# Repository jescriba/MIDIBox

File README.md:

MIDIBox is a basic midi controller with audio playback capabilities implemented for the AVR embedded environment _without_ Arduino libraries. 

Intro blog: https://jescriba.github.io/2019/12/22/midibox.html

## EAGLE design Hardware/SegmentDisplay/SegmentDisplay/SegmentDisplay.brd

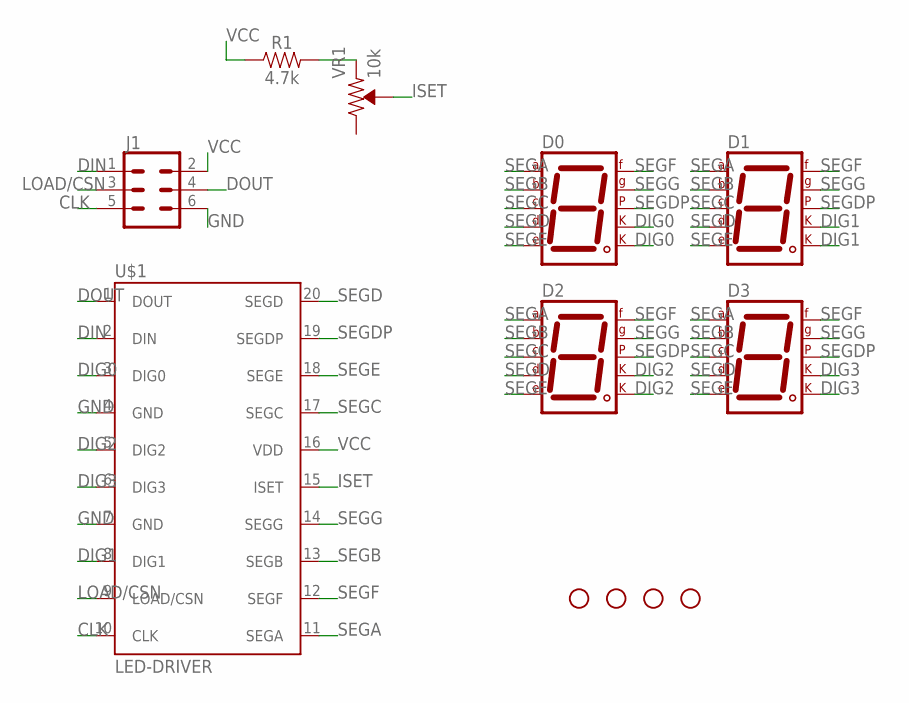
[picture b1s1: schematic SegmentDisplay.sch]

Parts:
D0, D1, D2, D3: 7SEG-CK; 7SEG-13
H1, H2, H3, H4: STAND-OFF
J1: CONN_03X2NO_SILK; 2X3-NS
R1: 4.7k; 0603
U$1: LED-DRIVER; SOIC20L
VR1: 10k; TRIMPOT-PTH-3386U

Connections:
CLK: J1.5, U$1.10 (CLK)
DIG0: D0.3 (CK1), D0.8 (CK2), U$1.3 (DIG0)
DIG1: D1.3 (CK1), D1.8 (CK2), U$1.8 (DIG1)
DIG2: D2.3 (CK1), D2.8 (CK2), U$1.5 (DIG2)
DIG3: D3.3 (CK1), D3.8 (CK2), U$1.6 (DIG3)
DIN: J1.1, U$1.2 (DIN)
DOUT: J1.4, U$1.1 (DOUT)
GND: J1.6, U$1.4 (GND), U$1.7 (GND)
ISET: U$1.15 (ISET), VR1.2 (WIPER)
LOAD/CSN: J1.3, U$1.9 (LOAD/CSN)
unnamed: R1.2, VR1.1 (CCW)
SEGA: D0.7 (A), D1.7 (A), D2.7 (A), D3.7 (A), U$1.11 (SEGA)
SEGB: D0.6 (B), D1.6 (B), D2.6 (B), D3.6 (B), U$1.13 (SEGB)
SEGC: D0.4 (C), D1.4 (C), D2.4 (C), D3.4 (C), U$1.17 (SEGC)
SEGD: D0.2 (D), D1.2 (D), D2.2 (D), D3.2 (D), U$1.20 (SEGD)
SEGDP: D0.5 (DP), D1.5 (DP), D2.5 (DP), D3.5 (DP), U$1.19 (SEGDP)
SEGE: D0.1 (E), D1.1 (E), D2.1 (E), D3.1 (E), U$1.18 (SEGE)
SEGF: D0.9 (F), D1.9 (F), D2.9 (F), D3.9 (F), U$1.12 (SEGF)
SEGG: D0.10 (G), D1.10 (G), D2.10 (G), D3.10 (G), U$1.14 (SEGG)
VCC: J1.2, R1.1, U$1.16 (VDD)

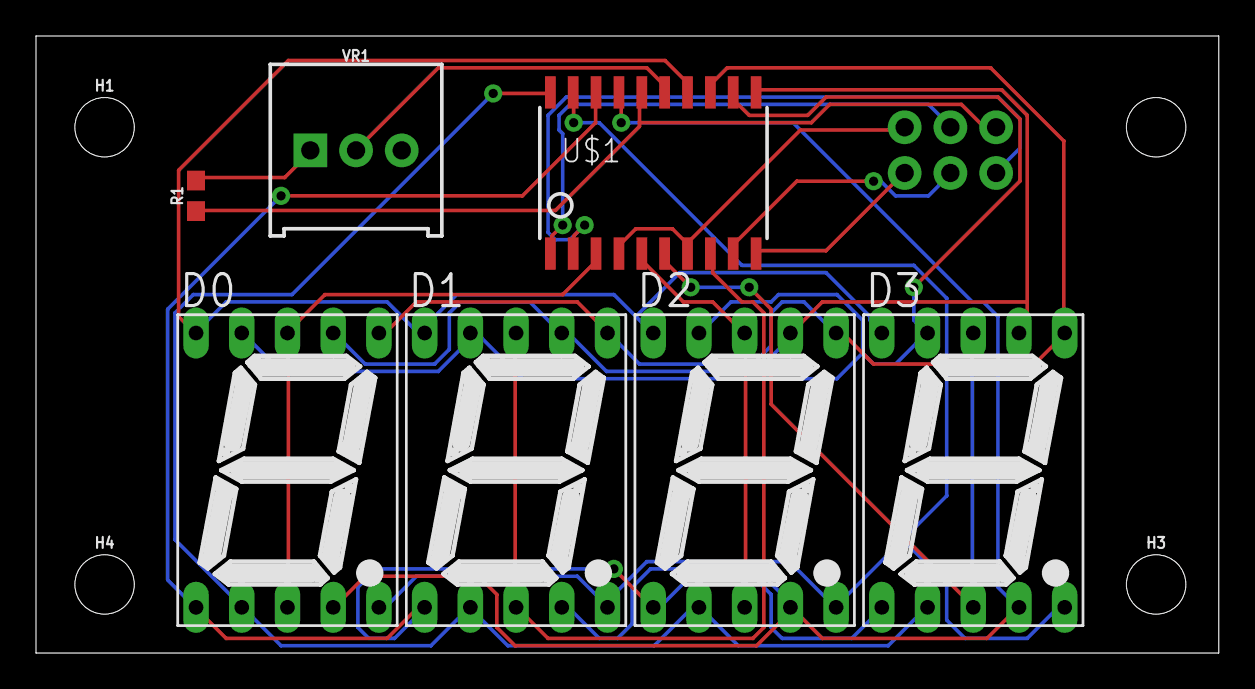
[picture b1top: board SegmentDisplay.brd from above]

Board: 2 copper layers, 65.7 x 34.3 mm, 12 parts (1 on the bottom side), 20 nets.

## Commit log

2019-12-23 Adds gitignore
2019-12-31 starts setting up isr
2020-01-01 Starts setting up basic interrupts and state tracking
2020-01-04 Adds enclosure design
2020-01-04 Remove gcode
2020-01-04 Revert "Remove gcode"
    This reverts commit bd896ab57b8ef60bbba11252f28b1cfd3d45b288.
2020-01-04 Attempt to remove gcode from language stats on github
2020-01-04 Starts setting up SPI interrupts
2020-01-04 Set theme jekyll-theme-minimal

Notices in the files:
parts and their libraries:
SparkFun-Connectors: Licensing: Creative Commons ShareAlike 4.0 International - https://creativecommons.org/licenses/by-sa/4.0
